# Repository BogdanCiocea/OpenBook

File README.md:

## PCB Description

#### ESP 
ESP32-C6-WROOM-1 is a general-purpose Wi-Fi, IEEE 802.15.4, and Bluetooth LE 
module. The rich set of peripherals and high performance make the module an 
ideal choice for smart homes, industrial automation, health care, consumer electronics, etc.

#### Absolute Maximum Ratings

| Symbol  | Parameter            | Min  | Max | Unit |
| ------- | -------------------- | ---- | --- | ---- |
| VDD33   | Power supply voltage | –0.3 | 3.6 | V    |
| T STORE | Storage temperature  | –40  | 105 | °C   |

##### CPU and On-Chip Memory
    • ESP32-C6 embedded, 32-bit RISC-V single-core microprocessor, up to 160 MHz
    • 320 KB ROM
    • 512 KB SRAM
    • 16 KB Low-power (LP) SRAM

#### W25Q512JVEIQ

External NOR flash memory offering high-density storage.

Specifications:

• Capacity: 512 Mbit (64 MB)
• Interface: SPI (Serial Peripheral Interface)
• Operating Voltage: 3.3 V
• Usage: Firmware, configuration data, graphical assets storage

#### MCP73831

Li-Po battery charger controller for efficient battery management.

Specifications:

• Charge Current: Programmable up to ~500 mA
• Charge Voltage: Fixed 4.2 V
• Input Voltage: 5 V (typically USB)
• Features: Thermal protection, automatic charge termination, LED charge status

#### XC6220A331MR-G

Low Dropout Voltage Regulator ensuring stable power.

Specifications:

• Output Voltage: 3.3 V
• Input Voltage Range: up to 6.0 V
• Current Rating: up to 700 mA

#### MAX17048G+T10

Battery Fuel Gauge IC for precise battery monitoring.

Specifications:

• Communication Interface: I²C
• Voltage Measurement Accuracy: ±7.5 mV
• Typical Current Consumption: 23 µA
• Usage: State-of-charge monitoring, battery life estimation

#### BME688

Advanced environmental sensor providing multiple parameters.

Specifications:

• Measurements: Temperature, Humidity, Pressure, VOC gas sensing
• Communication Interface: I²C
• Operating Voltage: 1.7 V – 3.6 V

#### DS3231SN

Highly accurate Real-Time Clock (RTC) module.

Specifications:

• Accuracy: ±2 ppm (~1 min/year)
• Communication Interface: I²C
• Operating Voltage: 2.3 V – 5.5 V
• Features: Integrated battery backup for uninterrupted timekeeping

#### FH34SRJ-24S-0.5SH(99)

FFC connector for reliable display connection.

Specifications:

• Pins: 24
• Pitch: 0.5 mm
• Mount Type: Surface Mount (SMD)
• Usage: Connecting E-paper displays

#### MBR0530

Schottky diode with low forward voltage.

Specifications:

• Maximum Current: 0.5 A
• Forward Voltage Drop: ~0.3-0.4 V
• Application: Reverse voltage protection, efficient switching

#### SI1308EDL-T1-GE3

Compact N-channel MOSFET for switching applications.

Specifications:

• Voltage Rating: 20 V
• Current Rating: ~2 A
• Usage: Switching operations in display driver circuits

#### CPH3225A

Supercapacitor designed for temporary backup power.

## Pins

#### SD Card (SPI)
    * pin 7 -> pin 27 (MISO)
    * pin 3 -> pin 7 (MOSI)
    * pin 2 -> pin 4 (SS_SD)
    * pin 5 -> pin 6 (SCK)

#### 3 Buttons
    • IO/BOOT on pin 15 
    • IO/CHANGE on pin 23
    • RESET on pin 3

#### Battery Charge Level
    • pin 7 -> pin 20 (SCL)
    • pin 8 -> pin 19 (SDA)

#### BME688
    • pin 6, 8, 2 -> pin 17 (I2C_PW)
    • pin 4 -> pin 20 (SCL)
    • pin 3 -> pin 19 (SDA)

##### RTC Module DS3231SN
    • pin 4 -> pin 16 (RTC_RST)
    • pin 16 -> pin 20 (SCL)
    • pin 15 -> pin 19 (SDA)
    • pin 3 -> pin 8 (INT_RTC)
    • pin 1 -> pin 9 (32KHz)

#### USB C connector & ESD protection
    • pin 1 -> pin 14 (USB_D+)
    • pin 3 -> pin 13 (USB_D-)

## Bill Of Materials (BOM):

| Component                   | Quantity | Price (€) | Link                                                                                                                            | Datasheet                                                                                                                             |
| :-------------------------- | -------- | --------- | ------------------------------------------------------------------------------------------------------------------------------- | ------------------------------------------------------------------------------------------------------------------------------------- |
| W25Q512JVEIQ                | 1        | 5.84      | https://eu.mouser.com/ProductDetail/Winbond/W25Q512JVEIQ?qs=l7cgNqFNU1jw6svr3at6tA%3D%3D                                        | https://eu.mouser.com/datasheet/2/949/Winbond_W25Q512JV_Datasheet-3240039.pdf                                                         |
| MAX17048G+T10               | 1        | 4.28      | https://eu.mouser.com/ProductDetail/Analog-Devices-Maxim-Integrated/MAX17048G%2bT10?qs=D7PJwyCwLAoGnnn8jEPRBQ%3D%3D             | https://eu.mouser.com/datasheet/2/609/MAX17048_MAX17049-3469099.pdf                                                                   |
| ESP32-C6-WROOM-1-N8         | 1        | 2.97      | https://eu.mouser.com/ProductDetail/Espressif-Systems/ESP32-C6-WROOM-1-N8?qs=8Wlm6%252BaMh8ST02Gmwp74cw%3D%3D                   | https://eu.mouser.com/datasheet/2/891/Espressif_ESP32_C6_WROOM_1__Datasheet_V0_1_PRELIMI-3239987.pdf                                  |
| 112A-TAAR-R03_ATTEND        | 1        | 1.05      | https://store.comet.srl.ro/Catalogue/Product/43497/                                                                             | https://store.comet.bg/download-file.php?id=27596                                                                                     |
| QWIIC_RIGHT_ANGLE           | 1        | 3.75      | https://eu.mouser.com/ProductDetail/Adafruit/4208?qs=PzGy0jfpSMtbScLbr0L5dw%3D%3D                                               | https://cdn-shop.adafruit.com/datasheets/HX8340-B_N__DS_preliminary_v01_071203.pdf                                                    |
| BD5229G-TR                  | 1        | 0.75      | https://eu.mouser.com/ProductDetail/ROHM-Semiconductor/BD5229G-TR?qs=4kLU8WoGk0vvnhrrYwdszw%3D%3D                               | https://fscdn.rohm.com/en/products/databook/datasheet/ic/power/voltage_detector/bd52xxg-e.pdf                                         |
| 1uF capacitor               | 1        | 0.13      | https://eu.mouser.com/ProductDetail/TAIYO-YUDEN/MAASL105CC7105MFCA01?qs=HFfMDpzxxd1Fn%2FInbJA7vw%3D%3D                          | https://eu.mouser.com/datasheet/2/396/TAIYO_YUDEN_04_27_2024_c_mlcc_A_e1-3451516.pdf                                                  |
| PGB1010603MR                | 6        | 0.40      | https://eu.mouser.com/ProductDetail/Littelfuse/PGB1010603MR?qs=gu7KAQ731URLg4GSnNNN7Q%3D%3D                                     | https://www.littelfuse.com/assetdocs/pulseguard-esd-suppressors-pgb1-datasheet?assetguid=8a337998-d54d-466b-be4e-dc5bcd1f9321         |
| MCP73831                    | 1        | 0.16      | https://eu.mouser.com/ProductDetail/Microchip-Technology/MCP73831T-5ACI-OT?qs=hH%252BOa0VZEiAcgAcEkuamXg%3D%3D                  | https://eu.mouser.com/datasheet/2/268/MCP73831_Family_Data_Sheet_DS20001984H-3441711.pdf                                              |
| 200 ohm resistor            | 1        | 0.10      | https://eu.mouser.com/ProductDetail/Wurth-Elektronik/560112110211?qs=sGAEpiMZZMtlubZbdhIBIIgWRUA0vTGpVUEy0IEGMjk%3D             | https://www.we-online.com/components/products/datasheet/560112110211.pdf                                                              |
| 2k ohm resistor             | 1        | 0.57      | https://eu.mouser.com/ProductDetail/Vishay-Beyschlag/MCS04020D2321BE100?qs=sGAEpiMZZMtlubZbdhIBINHXX5XJLWKoe%2FyX%252BeuBVuo%3D | https://www.vishay.com/docs/28700/mcx0x0xpre.pdf                                                                                      |
| XC6220A331MR-G              | 1        | 1.46      | https://eu.mouser.com/ProductDetail/Torex-Semiconductor/XC6220A331MR-G?qs=AsjdqWjXhJ8ZSWznL1J0gg%3D%3D                          | https://eu.mouser.com/datasheet/2/760/xc6220-3371556.pdf                                                                              |
| 100uF tant capacitor        | 1        | 25.19     | https://eu.mouser.com/ProductDetail/Vishay-Sprague/T97F107M035HAA?qs=kE1vTINknaW2TSWjulhndg%3D%3D                               | https://www.vishay.com/docs/40092/t97.pdf                                                                                             |
| 100k resistor               | 1        | 0.30      | https://eu.mouser.com/ProductDetail/Vishay-BC-Components/NTCS0402E3104JHT?qs=8wHch9UpSvY0bmpK2FbGWQ%3D%3D                       | https://www.vishay.com/docs/29003/ntcs0402e3t.pdf                                                                                     |
| CPH3225A                    | 1        | 2.33      | https://eu.mouser.com/ProductDetail/Seiko-Semiconductors/CPH3225A?qs=3etwrb1wR%252BhUOph6lAO7eg%3D%3D                           | https://eu.mouser.com/datasheet/2/360/Seiko_Instruments_MicroBattery_E_20230330_2024Jan_-3561061.pdf                                  |
| R_CAPACITOR                 | 1        | 0.12      | https://eu.mouser.com/ProductDetail/Panasonic/ERJ-2RKD15R0X?qs=8CJXEYeWfIrWZI67d3moiA%3D%3D                                     | https://industrial.panasonic.com/cdbs/www-data/pdf/RDA0000/AOA0000C304.pdf                                                            |
| FH34SRJ-24S-0.5SH_99_       | 1        | 2.60      | https://eu.mouser.com/ProductDetail/Hirose-Connector/FH34SRJ-24S-0.5SH99?qs=vcbW%252B4%252BSTIpKBl5ap9J8Fw%3D%3D                | https://eu.mouser.com/datasheet/2/185/FH34SRJ_24S_0_5SH_99__CL0580_1255_6_99_2DDrawing_0-1615044.pdf                                  |
| 0.1uF/50V capacitor         | 1        | 0.45      | https://eu.mouser.com/ProductDetail/KYOCERA-AVX/04025C104MAT2A?qs=sGAEpiMZZMukHu%252BjC5l7YbsWA2wxb4GLrh7pRRirNkk%3D            | https://eu.mouser.com/datasheet/2/40/KGM_X7R-3223212.pdf                                                                              |
| 1uF/50V capacitor           | 10       | 0.56      | https://eu.mouser.com/ProductDetail/TAIYO-YUDEN/MAASU32NSB7105KTCA01?qs=HFfMDpzxxd06eur8w0VYhA%3D%3D                            | https://eu.mouser.com/datasheet/2/396/TDK_4_24_2024_MAASU32NSB7105KTCA01_SS-3440852.pdf                                               |
| 2k ohm resistor             | 1        | 0.57      | https://eu.mouser.com/ProductDetail/Vishay-Beyschlag/MCS04020D2321BE100?qs=sGAEpiMZZMtlubZbdhIBINHXX5XJLWKoe%2FyX%252BeuBVuo%3D | https://www.vishay.com/docs/28700/mcx0x0xpre.pdf                                                                                      |
| BME688                      | 1        | 14.82     | https://eu.mouser.com/ProductDetail/Bosch-Sensortec/BME680-Shuttle-Board-3.0?qs=Wj%2FVkw3K%252BMABg5lm5143Ww%3D%3D              | https://eu.mouser.com/datasheet/2/783/bst_bme680_sf000-2486508.pdf                                                                    |
| 2.2 ohm resistor            | 1        | 0.15      | https://eu.mouser.com/ProductDetail/Panasonic/ERJ-PA2J2R2X?qs=sGAEpiMZZMtlubZbdhIBIKn8wLs5z3UnO%252BN6Zqj8Y2A%3D                | https://industrial.panasonic.com/cdbs/www-data/pdf/RDO0000/AOA0000C331.pdf                                                            |
| MBR0530                     | 3        | 0.18      | https://eu.mouser.com/ProductDetail/onsemi/MBR0530T3G?qs=3JMERSakebpEmdUS6GetdQ%3D%3D                                           | https://www.onsemi.com/download/data-sheet/pdf/mbr0530t1-d.pdf                                                                        |
| SI1308EDL-T1-GE3            | 1        | 0.42      | https://eu.mouser.com/ProductDetail/Vishay-Semiconductors/SI1308EDL-T1-GE3?qs=bX1%252BNvsK%2FBramh9tgpOaEw%3D%3D                | https://www.vishay.com/docs/63399/si1308edl.pdf                                                                                       |
| 0.47 ohm resistor           | 1        | 0.61      | https://eu.mouser.com/ProductDetail/ROHM-Semiconductor/UCR01MVPFLR470?qs=493kPxzlxfJor42A3tTE6g%3D%3D                           | https://fscdn.rohm.com/en/products/databook/datasheet/passive/resistor/chip_resistor/ucr-e.pdf                                        |
| 4.7uF/25V capacitor         | 1        | 0.27      | https://eu.mouser.com/ProductDetail/KYOCERA-AVX/04023D475MAT2A?qs=sGAEpiMZZMsh%252B1woXyUXj%252BCoURFk43JpehNp%2F1Fl9pk%3D      | https://eu.mouser.com/datasheet/2/40/cx5r-2835979.pdf                                                                                 |
| 68uH ind                    | 1        | 1.37      | https://store.comet.srl.ro/CatalogueFarnell/Product/1302649/                                                                    | https://www.we-online.com/components/products/datasheet/744043680.pdf                                                                 |
| 10uF capacitor              | 1        | 0.28      | https://eu.mouser.com/ProductDetail/KYOCERA-AVX/KGM05CS60J106MH?qs=9vOqFld9vZXSfhl2b2Q2gQ%3D%3D                                 | https://eu.mouser.com/datasheet/2/40/KGM_X6S-3223173.pdf                                                                              |
| SAMACSYS_PARTS_USB4110-GF-A | 1        | 1.18      | https://eu.mouser.com/ProductDetail/GCT/USB4110-GF-A?qs=KUoIvG%2F9IlYiZvIXQjyJeA%3D%3D                                          | https://eu.mouser.com/datasheet/2/837/GCT_USB4110_Product_Drawing___20k_cycles-3455479.pdf                                            |
| PFMF.050.1                  | 1        | 0.28      | https://eu.mouser.com/ProductDetail/Schurter/PFMF.050.2?qs=1auRipcfynCums5v1iucSA%3D%3D                                         | https://eu.mouser.com/datasheet/2/358/typ_PFMF-1275918.pdf                                                                            |
| 5k1 resistor                | 2        | 0.15      | https://eu.mouser.com/ProductDetail/Vishay-Beyschlag/MCS04020C5101FE000?qs=sGAEpiMZZMtlubZbdhIBIMAhWB6%252BRofmP3o4x7R7qwI%3D   | https://www.vishay.com/docs/28705/mcx0x0xpro.pdf                                                                                      |
| Battery                     | 1        | 10.45     | https://www.emag.ro/acumulator-li-polymer-2500mah-3-7v-104050-243/pd/D6VB6SMBM/                                                 | https://www.ufinebattery.com/images/upload/ufx0165-11-3-7v-2500mah-lithium-ion-battery-product-datasheet.pdf                          |
| Display                     | 1        | 44.12     | https://www.waveshare.com/7.5inch-e-paper.htm                                                                                   | https://files.waveshare.com/upload/6/60/7.5inch_e-Paper_V2_Specification.pdf                                                          |
| 100nF capacitor             | 8        | 0.013     | https://store.comet.srl.ro/Catalogue/Product/48939/                                                                             | https://store.comet.bg/download-file.php?id=11                                                                                        |
| 10k resistor                | 16       | 0.19      | https://eu.mouser.com/ProductDetail/Vishay/MCS04020D1022BE000?qs=pUKx8fyJudATYWOpd0Fc%2FA%3D%3D                                 | https://www.vishay.com/docs/28700/mcx0x0xpre.pdf                                                                                      |
| 4.7uF capacitor             | 5        | 0.82      | https://eu.mouser.com/ProductDetail/KEMET/C0402C475K8PACTU?qs=sGAEpiMZZMsh%252B1woXyUXj%252BeMYF%2FJh1ZHWLnD7xub%252BoY%3D      | https://eu.mouser.com/datasheet/2/447/KEM_C1006_X5R_SMD-3316465.pdf                                                                   |
| SD0805S020S1R0              | 2        | 0.30      | https://eu.mouser.com/ProductDetail/KYOCERA-AVX/SD0805S020S1R0?qs=jCA%252BPfw4LHbpkAoSnwrdjw%3D%3D                              | https://eu.mouser.com/ProductDetail/KYOCERA-AVX/SD0805S020S1R0?qs=jCA%252BPfw4LHbpkAoSnwrdjw%3D%3D                                    |
| DMG2305UX-7                 | 2        | 0.2       | https://store.comet.srl.ro/CatalogueFarnell/Product/1773598/                                                                    | https://4donline.ihs.com/images/VipMasterIC/IC/DIOD/DIOD-S-A0013043571/DIOD-S-A0013120650-1.pdf?hkey=6D3A4C79FDBF58556ACFDE234799DDF0 |

#### TOTAL: 145.79 euro

## Diagram

##### Design log:
Pentru PCB am acceptat 2 erori de Board Outline Clearence deoarece asa se spune
in OCW si 4 erori de Silkscreen Clearance deoarece nu puteam face nimic sa indepartez acele erori...asta e

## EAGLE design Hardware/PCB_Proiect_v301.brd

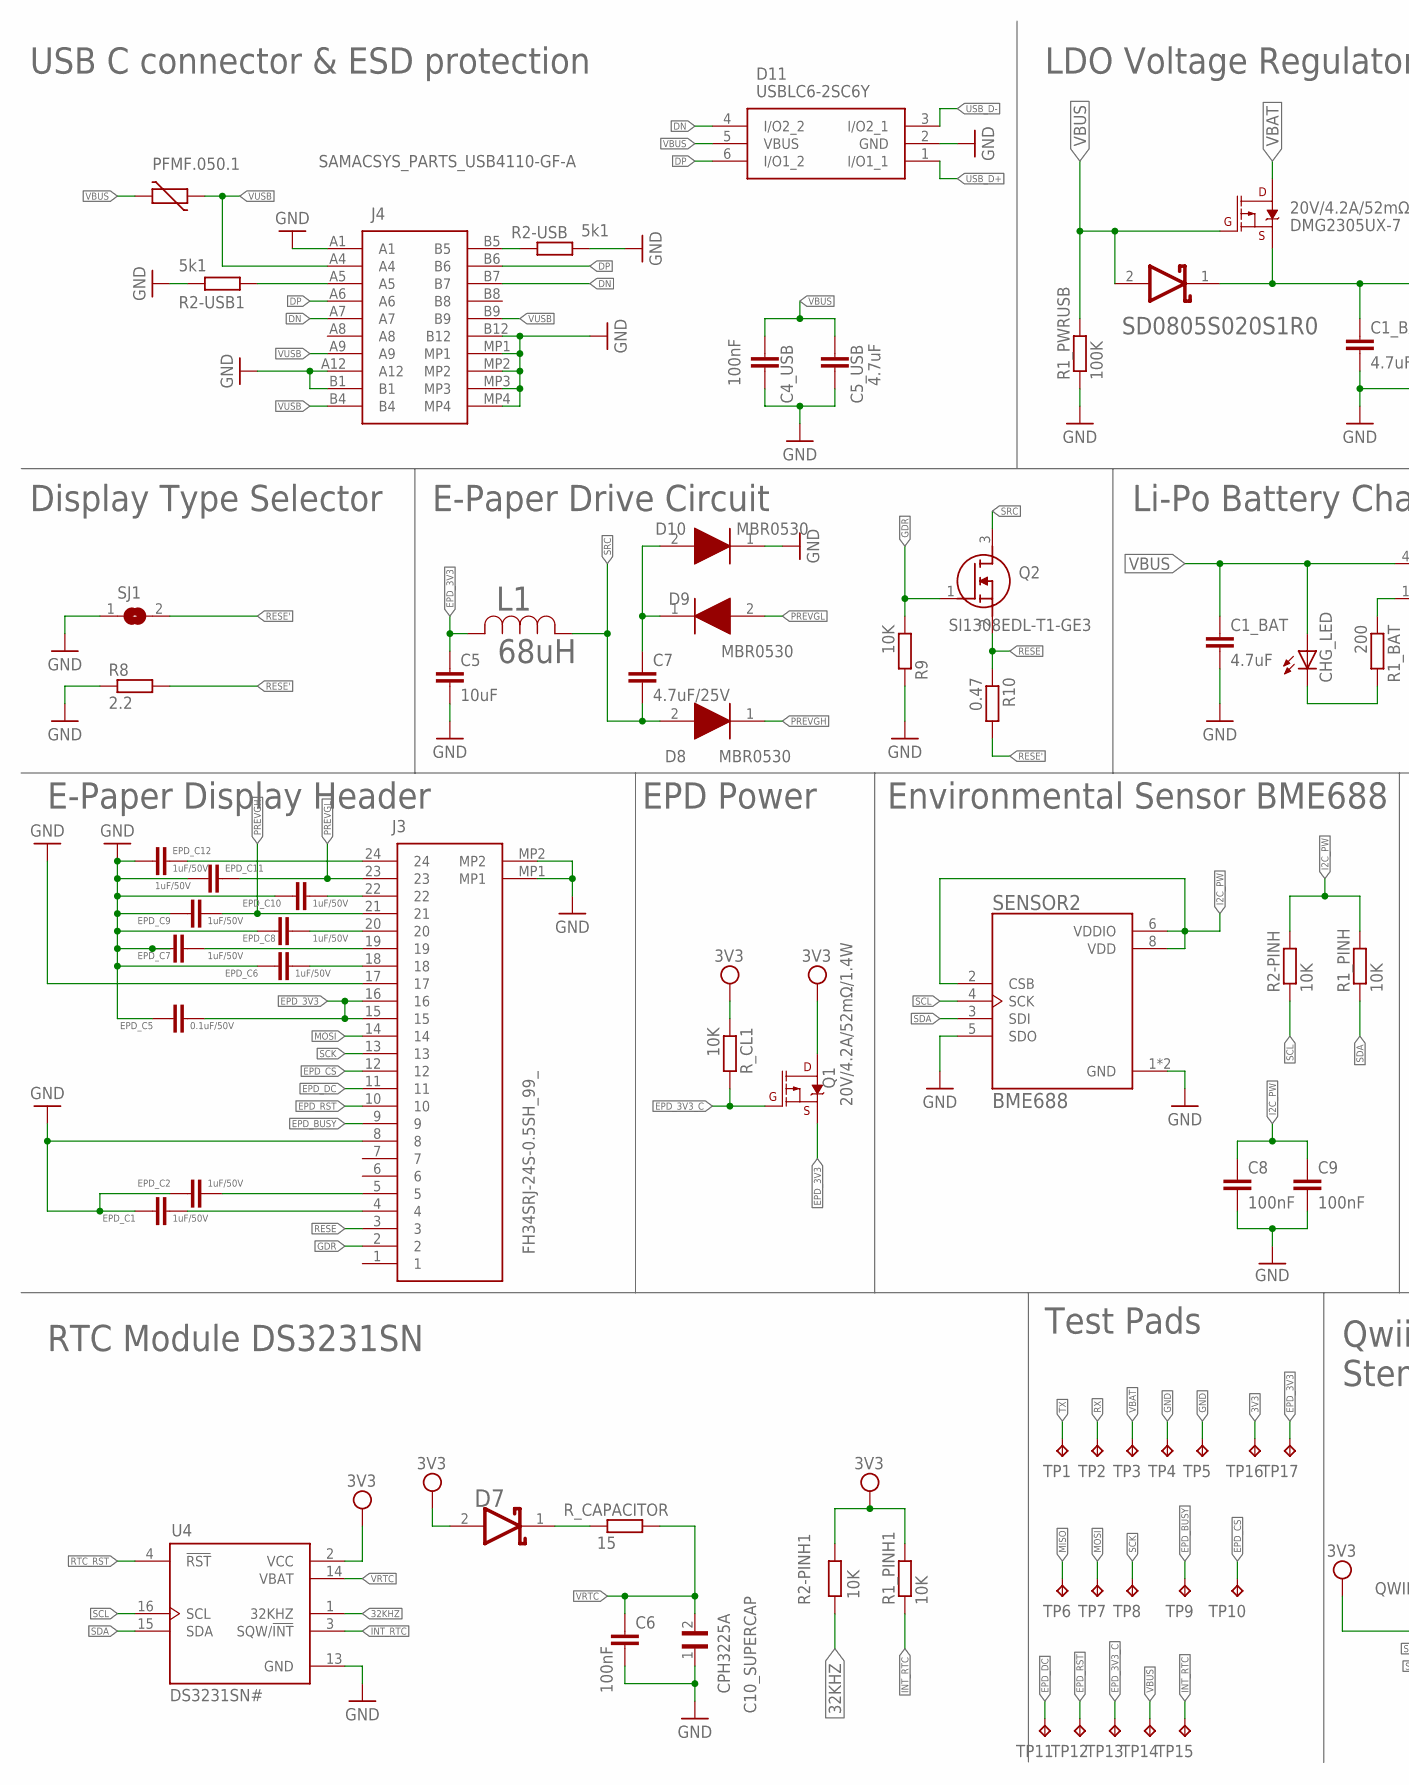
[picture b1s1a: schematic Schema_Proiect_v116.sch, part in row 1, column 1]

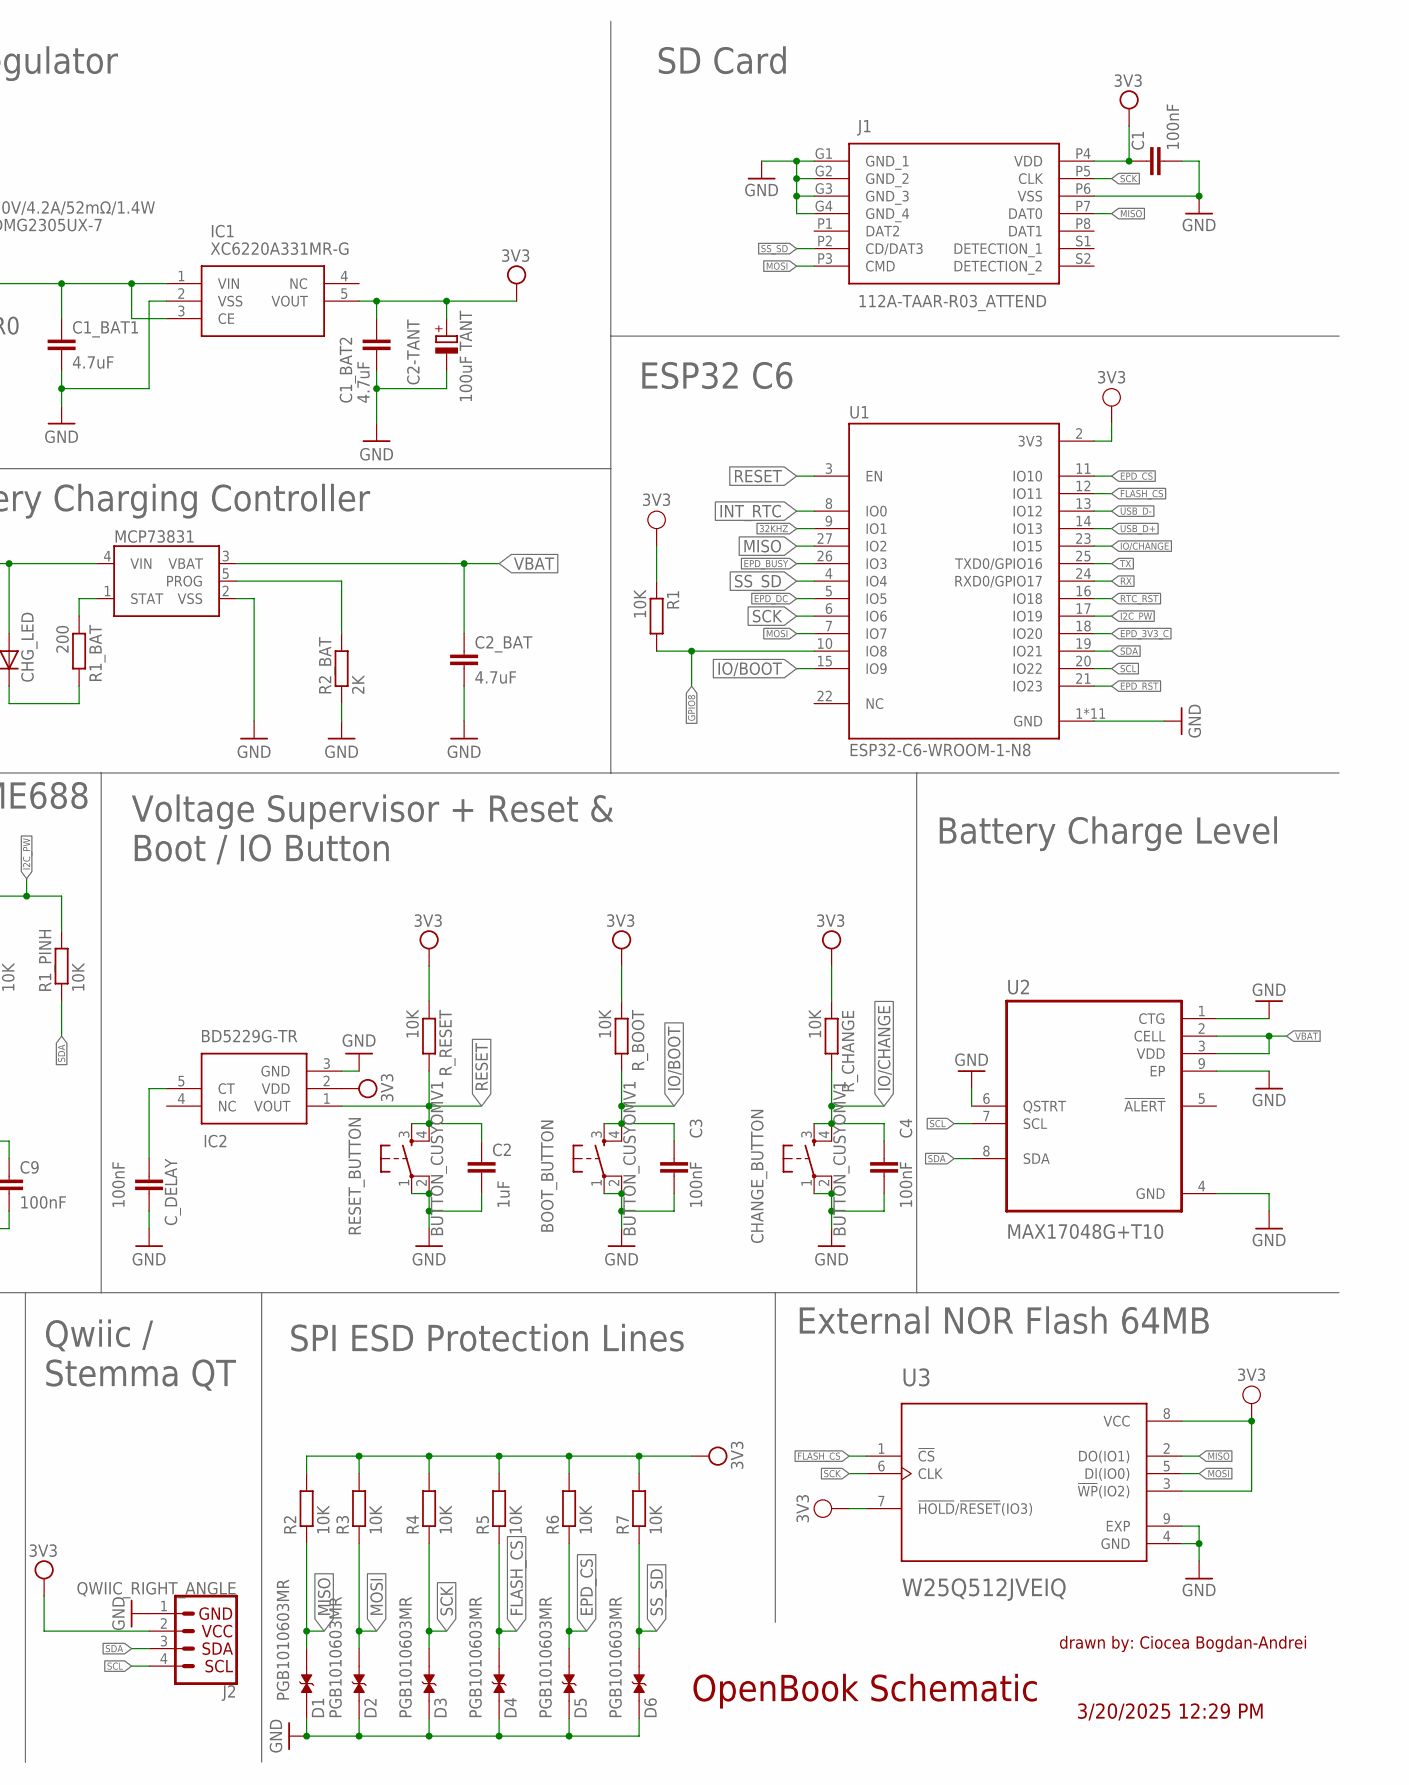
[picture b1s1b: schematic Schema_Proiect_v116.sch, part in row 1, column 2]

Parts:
BOOT_BUTTON: BUTTON_CUSYOMV1; MYBUTTON
C1, C3, C4, C4_USB, C6, C8, C9: 100nF; EAGLE-LTSPICE_C0402
C1_BAT, C1_BAT1, C1_BAT2, C2_BAT, C5_USB: 4.7uF; EAGLE-LTSPICE_C0402
C2: 1uF; EAGLE-LTSPICE_C0402
C2-TANT: 100uF TANT; RCL_CT3528
C5: 10uF; EAGLE-LTSPICE_C0402
C7: 4.7uF/25V; EAGLE-LTSPICE_C0402
C10_SUPERCAP: CPH3225A; CAPCP3225X100N
CHANGE_BUTTON: BUTTON_CUSYOMV1; MYBUTTON
CHG_LED: ADAFRUIT_LEDCHIP-LED0603; ADAFRUIT_CHIP-LED0603
C_DELAY: 100nF; EAGLE-LTSPICE_C0402
D1, D2, D3, D4, D5, D6: PGB1010603MR; DIOC1608X36N
D7: SD0805S020S1R0; ESP32_WROVER_AVX---SD0805S020S1R0_AVX_SD0805S020S1R0_0
D8, D9, D10: MBR0530; SOD3716X135N
D11: USBLC6-2SC6Y; SOT95P280X145-6N
DMG2305UX-7: 20V/4.2A/52mΩ/1.4W; ESP32_WROVER_SPARKFUN-DISCRETESEMI_SOT23-3
EPD_C1, EPD_C2, EPD_C6, EPD_C7, EPD_C8, EPD_C9, EPD_C10, EPD_C11, EPD_C12: 1uF/50V; EAGLE-LTSPICE_C0402
EPD_C5: 0.1uF/50V; EAGLE-LTSPICE_C0402
IC1: XC6220A331MR-G; SOT95P280X120-5N
IC2: BD5229G-TR; SOT95P280X125-5N
J1: 112A-TAAR-R03_ATTEND; 112ATAARR03ATTEND
J2: QWIIC_RIGHT_ANGLE; JST04_1MM_RA
J3: FH34SRJ-24S-0.5SH_99_; FH34SRJ24S05SH99
J4: SAMACSYS_PARTS_USB4110-GF-A; SAMACSYS_PARTS_USB4110GFA
L1: 68uH; IND_4828-WE-TPC_WRE
MCP73831: ESP32_WROVER_SPARKFUN-IC-POWER_MCP73831; ESP32_WROVER_SPARKFUN-IC-POWER_SOT23-5
PFMF.050.1: ESP32C6_VARISTORCN1812; ESP32C6_VARISTOR_CT/CN1812
Q1: 20V/4.2A/52mΩ/1.4W; ESP32_WROVER_SPARKFUN-DISCRETESEMI_SOT23-3
Q2: SI1308EDL-T1-GE3; SOT65P210X110-3N
R1, R1_PINH, R1_PINH1, R2, R2-PINH, R2-PINH1, R3, R4, R5, R6, R7, R9: 10K; ESP32_WROVER_EAGLE-LTSPICE_R0402
R1_BAT: 200; ESP32_WROVER_EAGLE-LTSPICE_R0402
R1_PWRUSB: 100K; ESP32_WROVER_EAGLE-LTSPICE_R0402
R2-USB, R2-USB1: 5k1; ESP32_WROVER_EAGLE-LTSPICE_R0402
R2_BAT: 2K; ESP32_WROVER_EAGLE-LTSPICE_R0402
R8: 2.2; ESP32_WROVER_EAGLE-LTSPICE_R0402
R10: 0.47; ESP32_WROVER_EAGLE-LTSPICE_R0402
RESET_BUTTON: BUTTON_CUSYOMV1; MYBUTTON
R_BOOT: 10K; ESP32_WROVER_EAGLE-LTSPICE_R0402
R_CAPACITOR: 15; ESP32_WROVER_EAGLE-LTSPICE_R0402
R_CHANGE: 10K; ESP32_WROVER_EAGLE-LTSPICE_R0402
R_CL1: 10K; ESP32_WROVER_EAGLE-LTSPICE_R0402
R_RESET: 10K; ESP32_WROVER_EAGLE-LTSPICE_R0402
SD0805S020S1R0: ESP32_WROVER_AVX---SD0805S020S1R0_AVX_SD0805S020S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; ESP32_WROVER_AVX---SD0805S020S1R0_AVX_SD0805S020S1R0_0
SENSOR2: BME688; ESP32_WROVER_BME680_PSON80P300X300X100-8N
SJ1: SJ
TP1: TX; TP20R
TP2: RX; TP20R
TP3: VBAT; TP20R
TP4, TP5: GND; TP20R
TP6: MISO; TP20R
TP7: MOSI; TP20R
TP8: SCK; TP20R
TP9: EPD_BUSY; TP20R
TP10: EPD_CS; TP20R
TP11: EPD_DC; TP20R
TP12: EPD_RST; TP20R
TP13: EPD_3V3_C; TP20R
TP14: VBUS; TP20R
TP15: INT_RTC; TP20R
TP16: 3V3; TP20R
TP17: EPD_3V3; TP20R
U1: ESP32-C6-WROOM-1-N8; XCVR_ESP32-C6-WROOM-1-N8
U2: MAX17048G+T10; SON50P200X200X80-9N
U3: W25Q512JVEIQ; SON127P600X800X80-9N
U4: DS3231SN#; SOIC127P1032X265-16N

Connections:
3V3: C1.1, C1_BAT2.1, C2-TANT.+, D7.2 (ANODE), IC1.5 (VOUT), IC2.2 (VDD), J1.P4 (VDD), J2.2, Q1.3 (D), R1.1, R1_PINH1.2, R2.2, R2-PINH1.1, R3.2, R4.2, R5.2, R6.2, R7.2, R_BOOT.1, R_CHANGE.1, R_CL1.1, R_RESET.1, TP16.TP, U1.2 (3V3), U3.3 (!WP!(IO2)), U3.7 (!HOLD!/!RESET!(IO3)), U3.8 (VCC), U4.2 (VCC)
32KHZ: R2-PINH1.2, U1.9 (IO1), U4.1 (32KHZ)
DN: D11.4 (I/O2_2), J4.A7, J4.B7
DP: D11.6 (I/O1_2), J4.A6, J4.B6
EPD_3V3: C5.1, EPD_C5.1, J3.15, J3.16, L1.2, Q1.2 (S), TP17.TP
EPD_3V3_C: Q1.1 (G), R_CL1.2, TP13.TP, U1.18 (IO20)
EPD_BUSY: J3.9, TP9.TP, U1.26 (IO3)
EPD_CS: D5.2, J3.12, R6.1, TP10.TP, U1.11 (IO10)
EPD_DC: J3.11, TP11.TP, U1.5 (IO5)
EPD_RST: J3.10, TP12.TP, U1.21 (IO23)
FLASH_CS: D4.2, R5.1, U1.12 (IO11), U3.1 (!CS)
GDR: J3.2, Q2.1 (G), R9.1
GND: BOOT_BUTTON.1, BOOT_BUTTON.2, C1.2, C1_BAT.2, C1_BAT1.2, C1_BAT2.2, C2.2, C2-TANT.-, C2_BAT.2, C3.2, C4.2, C4_USB.2, C5.2, C5_USB.2, C6.2, C8.2, C9.2, C10_SUPERCAP.1, CHANGE_BUTTON.1, CHANGE_BUTTON.2, C_DELAY.2, D1.1, D2.1, D3.1, D4.1, D5.1, D6.1, D10.1 (K), D11.2 (GND), EPD_C1.2, EPD_C2.2, EPD_C5.2, EPD_C6.2, EPD_C7.2, EPD_C8.2, EPD_C9.2, EPD_C10.2, EPD_C11.2, EPD_C12.2, IC1.2 (VSS), IC2.3 (GND), J1.G1 (GND_1), J1.G2 (GND_2), J1.G3 (GND_3), J1.G4 (GND_4), J1.P6 (VSS), J2.1, J3.8, J3.17, J3.MP1, J3.MP2, J4.A1, J4.A12, J4.B1, J4.B12, J4.MP1, J4.MP2, J4.MP3, J4.MP4, MCP73831.2 (VSS), R1_PWRUSB.1, R2-USB.2, R2-USB1.1, R2_BAT.1, R8.1, R9.2, RESET_BUTTON.1, RESET_BUTTON.2, SENSOR2.1 (GND), SENSOR2.5 (SDO), SENSOR2.7 (GND), SJ1.1, TP4.TP, TP5.TP, U1.1 (GND), U1.28 (GND), U1.29_1 (GND), U1.29_2 (GND), U1.29_3 (GND), U1.29_4 (GND), U1.29_5 (GND), U1.29_6 (GND), U1.29_7 (GND), U1.29_8 (GND), U1.29_9 (GND), U2.1 (CTG), U2.4 (GND), U2.6 (QSTRT), U2.9 (EP), U3.4 (GND), U3.9 (EXP), U4.13 (GND)
GPIO8: R1.2, U1.10 (IO8)
I2C_PW: C8.1, C9.1, R1_PINH.2, R2-PINH.2, SENSOR2.2 (CSB), SENSOR2.6 (VDDIO), SENSOR2.8 (VDD), U1.17 (IO19)
INT_RTC: R1_PINH1.1, TP15.TP, U1.8 (IO0), U4.3 (SQW/!INT)
IO/BOOT: BOOT_BUTTON.3, BOOT_BUTTON.4, C3.1, R_BOOT.2, U1.15 (IO9)
IO/CHANGE: C4.1, CHANGE_BUTTON.3, CHANGE_BUTTON.4, R_CHANGE.2, U1.23 (IO15)
MISO: D1.2, J1.P7 (DAT0), R2.1, TP6.TP, U1.27 (IO2), U3.2 (DO(IO1))
MOSI: D2.2, J1.P3 (CMD), J3.14, R3.1, TP7.TP, U1.7 (IO7), U3.5 (DI(IO0))
unnamed: CHG_LED.C, R1_BAT.2
unnamed: D7.1 (CATHODE), R_CAPACITOR.2
unnamed: C_DELAY.1, IC2.5 (CT)
unnamed: C1_BAT1.1, DMG2305UX-7.2 (S), IC1.1 (VIN), IC1.3 (CE), SD0805S020S1R0.1 (CATHODE)
unnamed: MCP73831.5 (PROG), R2_BAT.2
unnamed: MCP73831.1 (STAT), R1_BAT.1
unnamed: EPD_C12.1, J3.24
unnamed: EPD_C7.1, J3.19
unnamed: EPD_C1.1, J3.4
unnamed: EPD_C2.1, J3.5
unnamed: EPD_C10.1, J3.22
unnamed: EPD_C8.1, J3.20
unnamed: C7.1, D9.1 (K), D10.2 (A)
unnamed: J4.B5, R2-USB.1
unnamed: J4.A5, R2-USB1.2
unnamed: EPD_C6.1, J3.18
PREVGH: D8.1 (K), EPD_C9.1, J3.21
PREVGL: D9.2 (A), EPD_C11.1, J3.23
RESE: J3.3, Q2.2 (S), R10.1
RESE': R8.2, R10.2, SJ1.2
RESET: C2.1, IC2.1 (VOUT), RESET_BUTTON.3, RESET_BUTTON.4, R_RESET.2, U1.3 (EN)
RTC_RST: U1.16 (IO18), U4.4 (!RST)
RX: TP2.TP, U1.24 (RXD0/GPIO17)
SCK: D3.2, J1.P5 (CLK), J3.13, R4.1, TP8.TP, U1.6 (IO6), U3.6 (CLK)
SCL: J2.4, R2-PINH.1, SENSOR2.4 (SCK), U1.20 (IO22), U2.7 (SCL), U4.16 (SCL)
SDA: J2.3, R1_PINH.1, SENSOR2.3 (SDI), U1.19 (IO21), U2.8 (SDA), U4.15 (SDA)
SRC: C7.2, D8.2 (A), L1.1, Q2.3 (D)
SS_SD: D6.2, J1.P2 (CD/DAT3), R7.1, U1.4 (IO4)
TX: TP1.TP, U1.25 (TXD0/GPIO16)
USB_D+: D11.1 (I/O1_1), U1.14 (IO13)
USB_D-: D11.3 (I/O2_1), U1.13 (IO12)
VBAT: C2_BAT.1, DMG2305UX-7.3 (D), MCP73831.3 (VBAT), TP3.TP, U2.2 (CELL), U2.3 (VDD)
VBUS: C1_BAT.1, C4_USB.1, C5_USB.1, CHG_LED.A, D11.5 (VBUS), DMG2305UX-7.1 (G), MCP73831.4 (VIN), PFMF.050.1.2, R1_PWRUSB.2, SD0805S020S1R0.2 (ANODE), TP14.TP
VRTC: C6.1, C10_SUPERCAP.2, R_CAPACITOR.1, U4.14 (VBAT)
VUSB: J4.A4, J4.A9, J4.B4, J4.B9, PFMF.050.1.1

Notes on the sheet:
drawn by: Ciocea Bogdan-Andrei
OpenBook Schematic
External NOR Flash 64MB
Battery Charge Level
SD Card
SPI ESD Protection Lines
Qwiic / Stemma QT
Test Pads
Voltage Supervisor + Reset & Boot / IO Button
ESP32 C6
RTC Module DS3231SN
USB C connector & ESD protection
LDO Voltage Regulator
Li-Po Battery Charging Controller
E-Paper Drive Circuit
Display Type Selector
Environmental Sensor BME688
EPD Power
E-Paper Display Header
3/20/2025 12:29 PM

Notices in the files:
parts and their libraries:
COPYRIGHT: Copyright (C) 2024 Ultra Librarian. All rights reserved.
